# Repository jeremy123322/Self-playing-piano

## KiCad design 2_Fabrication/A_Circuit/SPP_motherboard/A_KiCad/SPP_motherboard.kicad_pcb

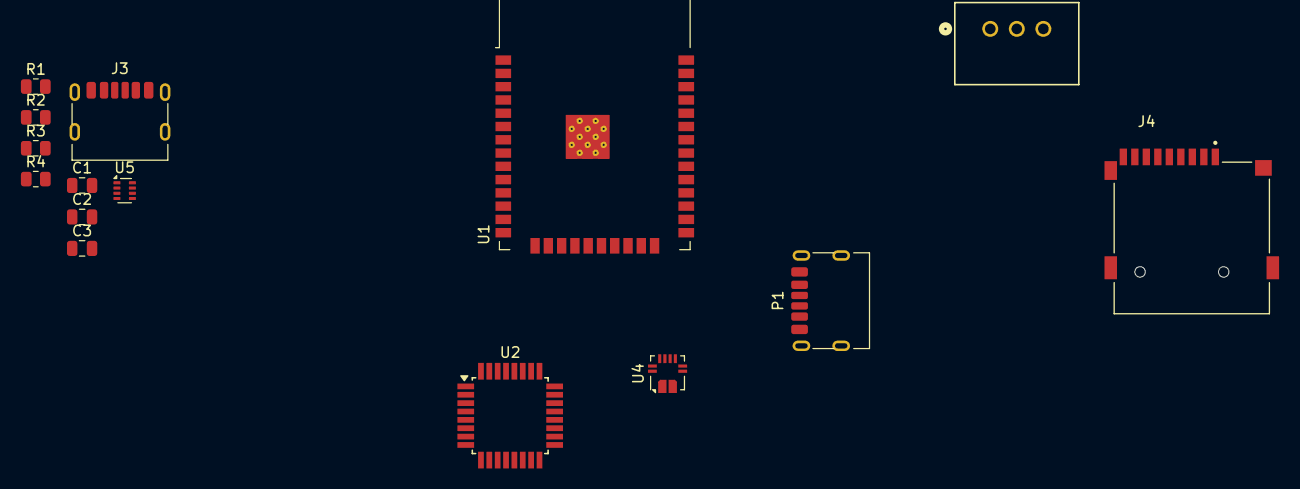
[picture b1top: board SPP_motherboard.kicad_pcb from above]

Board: 2 copper layers, 15 parts (0 on the bottom side), 13 nets, no tracks yet.

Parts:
C1: 100nF; C_0805_2012Metric
C2: 10uF; C_0805_2012Metric
C3: 22uF; C_0805_2012Metric
J3: USB_C_Receptacle_USB2.0_14P; USB_C_Receptacle_HRO_TYPE-C-31-M-17
J4: Micro_SD_Card; CUI_MSD-1-A
P1: USB_C_Plug_USB2.0; USB_C_Receptacle_HRO_TYPE-C-31-M-17
R1, R2: 5.1k; R_0805_2012Metric
R3, R4: R; R_0805_2012Metric
U1: ESP32-WROOM-32
U2: ATmega328P-A; TQFP-32_7x7mm_P0.8mm
U2#2: RBT10W24S05; RBT10W24S05_XPP_XPR
U4: ACS711xEXLT-31AB; Allegro_QFN-12-10-1EP_3x3mm_P0.5mm
U5: TPS2116DRL; SOT-583-8

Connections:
+3V3: C1.1, C3.1, U4.10 (VCC)
+5V,DC/DC: U2#2.3 (Vout), U5.6 (VIN2)
+24V: U2#2.1 (Vin), U4.2 (IP-)
GND: C1.2, C2.2, C3.2, J3.A12 (GND), J3.B12 (GND), J3.S1 (SHIELD), R1.2, R2.2, R4.2, U2#2.2 (GND), U4.3 (GND), U5.1 (GND)
unnamed: J3.A5 (CC1), R2.1
unnamed: J3.B5 (CC2), R1.1
unnamed: P1.A12 (GND), P1.B12 (GND)
unnamed: P1.A9 (VBUS), P1.B9 (VBUS)
unnamed: U1.1 (GND), U1.15 (GND), U1.38 (GND), U1.39 (GND)
unnamed: U2.3 (GND), U2.5 (GND), U2.21 (GND)
unnamed: U2.4 (VCC), U2.6 (VCC)
unnamed: R3.2, R4.1, U5.4 (PR1)
VBUS: J3.A9 (VBUS), J3.B9 (VBUS), R3.1, U5.3 (VIN1), U5.5 (MODE)

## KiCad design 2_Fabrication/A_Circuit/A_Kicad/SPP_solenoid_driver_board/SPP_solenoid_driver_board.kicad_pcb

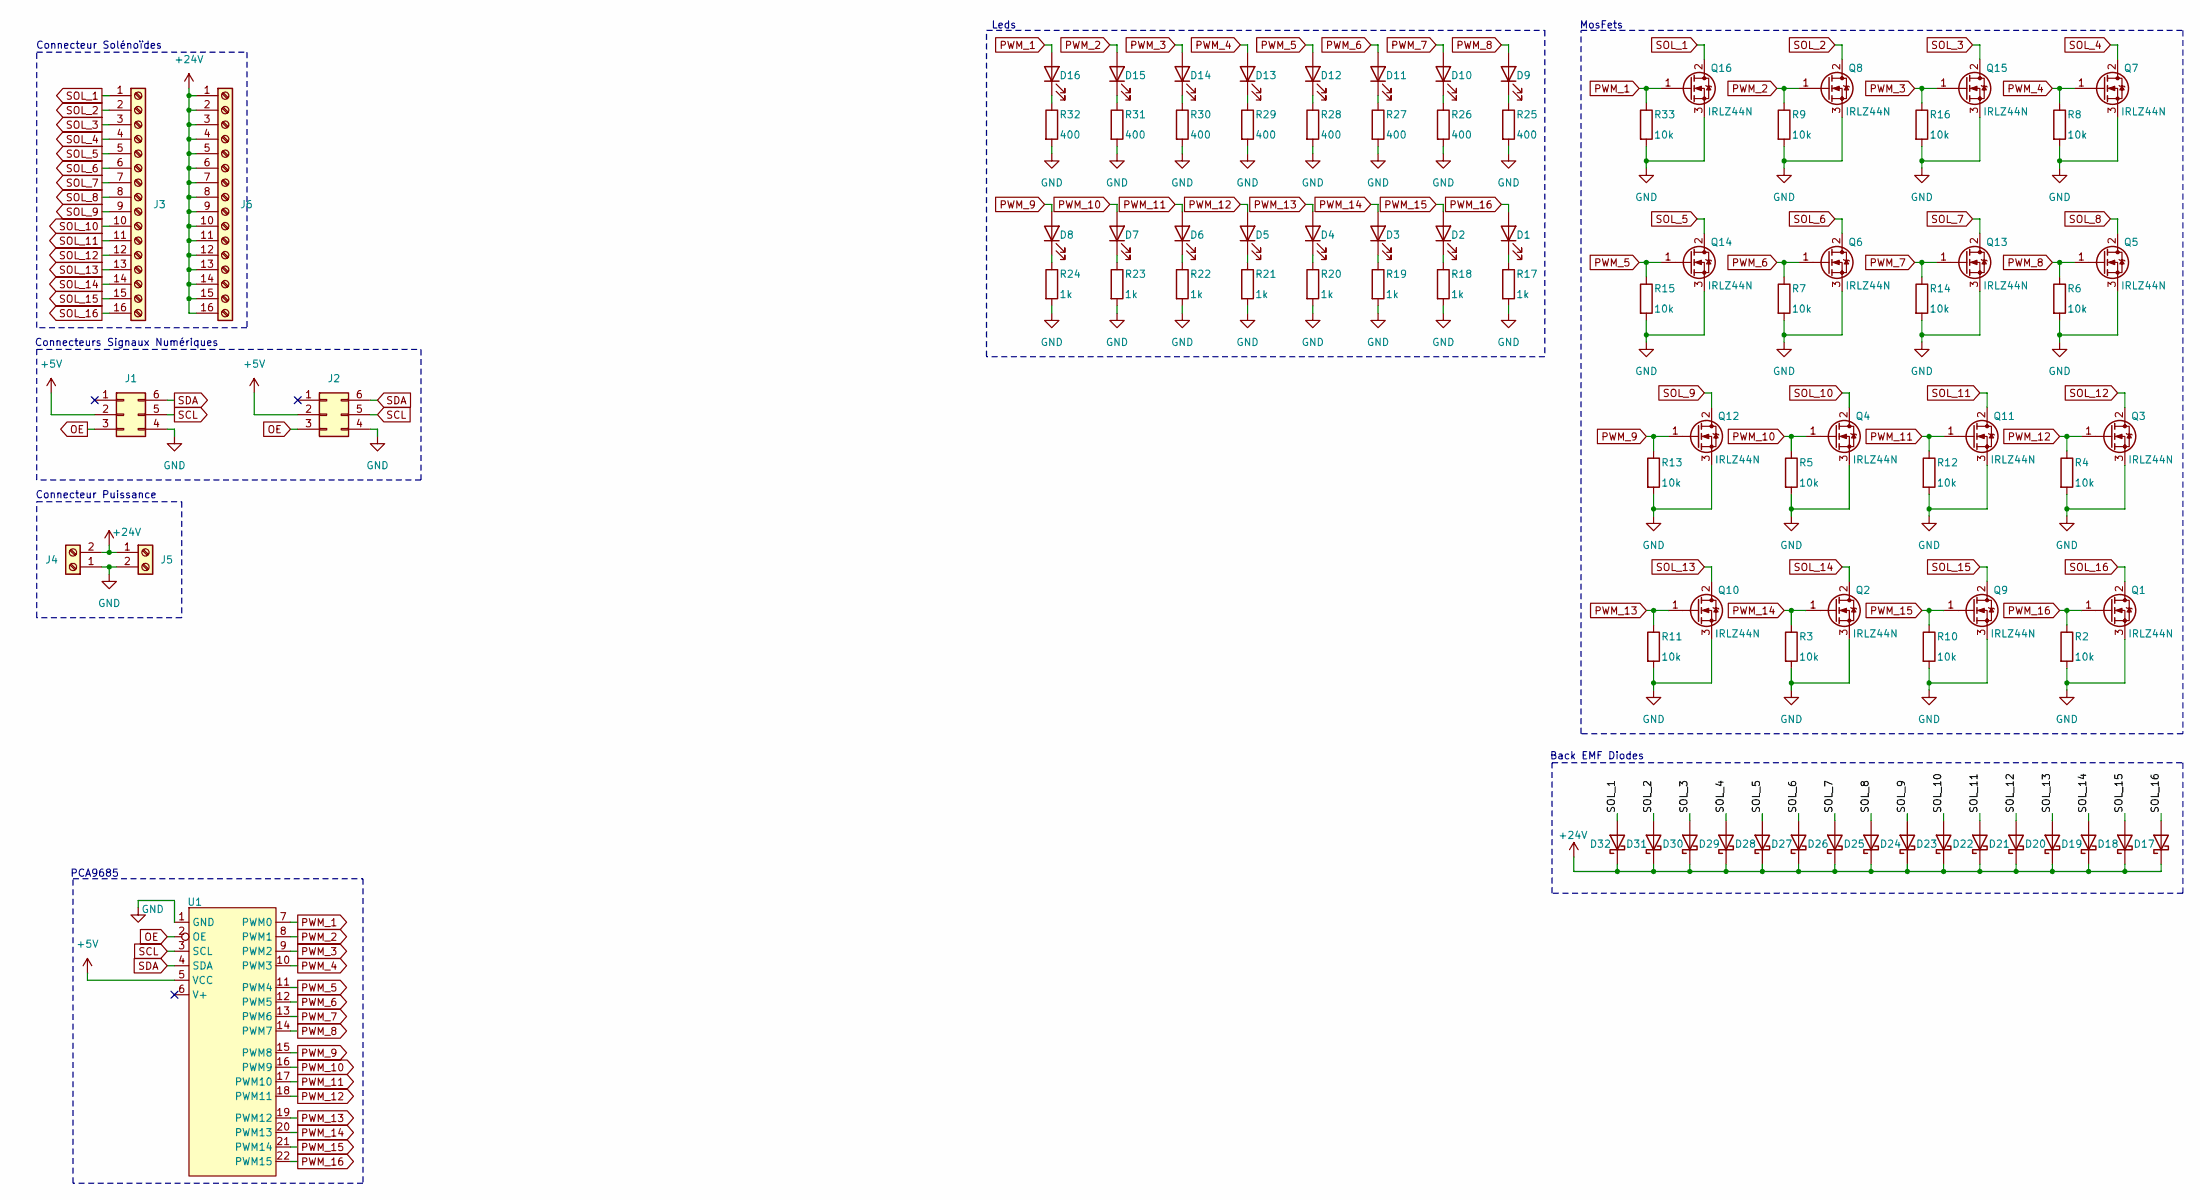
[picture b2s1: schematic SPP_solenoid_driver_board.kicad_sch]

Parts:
D1, D2, D3, D4, D5, D6, D7, D8, D9, D10, D11, D12, D13, D14, D15, D16: LED; LED_D5.0mm_Clear
D17, D18, D19, D20, D21, D22, D23, D24, D25, D26, D27, D28, D29, D30, D31, D32: 1N5819; D_DO-41_SOD81_P10.16mm_Horizontal
J1, J2: Conn_02x03_Counter_Clockwise; IDC-Header_2x03_P2.54mm_Vertical
J3, J6: Screw_Terminal_01x16; TerminalBlock_Phoenix_PT-1,5-16-5.0-H_1x16_P5.00mm_Horizont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
J4, J5: Screw_Terminal_01x02; TerminalBlock_Phoenix_MKDS-1,5-2_1x02_P5.00mm_Horizontal
Q1, Q2, Q3, Q4, Q5, Q6, Q7, Q8, Q9, Q10, Q11, Q12, Q13, Q14, Q15, Q16: IRLZ44N; TO-220-3_Vertical
R2, R3, R4, R5, R6, R7, R8, R9, R10, R11, R12, R13, R14, R15, R16, R33: 10k; R_1206_3216Metric
R17, R18, R19, R20, R21, R22, R23, R24: 1k; R_1206_3216Metric
R25, R26, R27, R28, R29, R30, R31, R32: 400; R_1206_3216Metric
U1: PCA9685_Devkit

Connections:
+5V: J1.2, J2.2, U1.5 (VCC)
+24V: D17.1 (K), D18.1 (K), D19.1 (K), D20.1 (K), D21.1 (K), D22.1 (K), D23.1 (K), D24.1 (K), D25.1 (K), D26.1 (K), D27.1 (K), D28.1 (K), D29.1 (K), D30.1 (K), D31.1 (K), D32.1 (K), J4.2, J5.1, J6.1, J6.2, J6.3, J6.4, J6.5, J6.6, J6.7, J6.8, J6.9, J6.10, J6.11, J6.12, J6.13, J6.14, J6.15, J6.16
GND: J1.4, J2.4, J4.1, J5.2, Q1.3 (S), Q2.3 (S), Q3.3 (S), Q4.3 (S), Q5.3 (S), Q6.3 (S), Q7.3 (S), Q8.3 (S), Q9.3 (S), Q10.3 (S), Q11.3 (S), Q12.3 (S), Q13.3 (S), Q14.3 (S), Q15.3 (S), Q16.3 (S), R2.2, R3.2, R4.2, R5.2, R6.2, R7.2, R8.2, R9.2, R10.2, R11.2, R12.2, R13.2, R14.2, R15.2, R16.2, R17.2, R18.2, R19.2, R20.2, R21.2, R22.2, R23.2, R24.2, R25.2, R26.2, R27.2, R28.2, R29.2, R30.2, R31.2, R32.2, R33.2, U1.1 (GND)
unnamed: D1.1 (K), R17.1
unnamed: D2.1 (K), R18.1
unnamed: D3.1 (K), R19.1
unnamed: D4.1 (K), R20.1
unnamed: D5.1 (K), R21.1
unnamed: D6.1 (K), R22.1
unnamed: D7.1 (K), R23.1
unnamed: D8.1 (K), R24.1
unnamed: D9.1 (K), R25.1
unnamed: D10.1 (K), R26.1
unnamed: D11.1 (K), R27.1
unnamed: D12.1 (K), R28.1
unnamed: D13.1 (K), R29.1
unnamed: D14.1 (K), R30.1
unnamed: D15.1 (K), R31.1
unnamed: D16.1 (K), R32.1
OE: J1.3, J2.3, U1.2 (OE)
PWM_1: D16.2 (A), Q16.1 (G), R33.1, U1.7 (PWM0)
PWM_2: D15.2 (A), Q8.1 (G), R9.1, U1.8 (PWM1)
PWM_3: D14.2 (A), Q15.1 (G), R16.1, U1.9 (PWM2)
PWM_4: D13.2 (A), Q7.1 (G), R8.1, U1.10 (PWM3)
PWM_5: D12.2 (A), Q14.1 (G), R15.1, U1.11 (PWM4)
PWM_6: D11.2 (A), Q6.1 (G), R7.1, U1.12 (PWM5)
PWM_7: D10.2 (A), Q13.1 (G), R14.1, U1.13 (PWM6)
PWM_8: D9.2 (A), Q5.1 (G), R6.1, U1.14 (PWM7)
PWM_9: D8.2 (A), Q12.1 (G), R13.1, U1.15 (PWM8)
PWM_10: D7.2 (A), Q4.1 (G), R5.1, U1.16 (PWM9)
PWM_11: D6.2 (A), Q11.1 (G), R12.1, U1.17 (PWM10)
PWM_12: D5.2 (A), Q3.1 (G), R4.1, U1.18 (PWM11)
PWM_13: D4.2 (A), Q10.1 (G), R11.1, U1.19 (PWM12)
PWM_14: D3.2 (A), Q2.1 (G), R3.1, U1.20 (PWM13)
PWM_15: D2.2 (A), Q9.1 (G), R10.1, U1.21 (PWM14)
PWM_16: D1.2 (A), Q1.1 (G), R2.1, U1.22 (PWM15)
SCL: J1.5, J2.5, U1.3 (SCL)
SDA: J1.6, J2.6, U1.4 (SDA)
SOL_1: D32.2 (A), J3.1, Q16.2 (D)
SOL_2: D31.2 (A), J3.2, Q8.2 (D)
SOL_3: D30.2 (A), J3.3, Q15.2 (D)
SOL_4: D29.2 (A), J3.4, Q7.2 (D)
SOL_5: D28.2 (A), J3.5, Q14.2 (D)
SOL_6: D27.2 (A), J3.6, Q6.2 (D)
SOL_7: D26.2 (A), J3.7, Q13.2 (D)
SOL_8: D25.2 (A), J3.8, Q5.2 (D)
SOL_9: D24.2 (A), J3.9, Q12.2 (D)
SOL_10: D23.2 (A), J3.10, Q4.2 (D)
SOL_11: D22.2 (A), J3.11, Q11.2 (D)
SOL_12: D21.2 (A), J3.12, Q3.2 (D)
SOL_13: D20.2 (A), J3.13, Q10.2 (D)
SOL_14: D19.2 (A), J3.14, Q2.2 (D)
SOL_15: D18.2 (A), J3.15, Q9.2 (D)
SOL_16: D17.2 (A), J3.16, Q1.2 (D)

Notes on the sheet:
Back EMF Diodes
MosFets
Leds
PCA9685
Connecteurs Signaux Numériques
Connecteur Puissance
Connecteur Solénoïdes

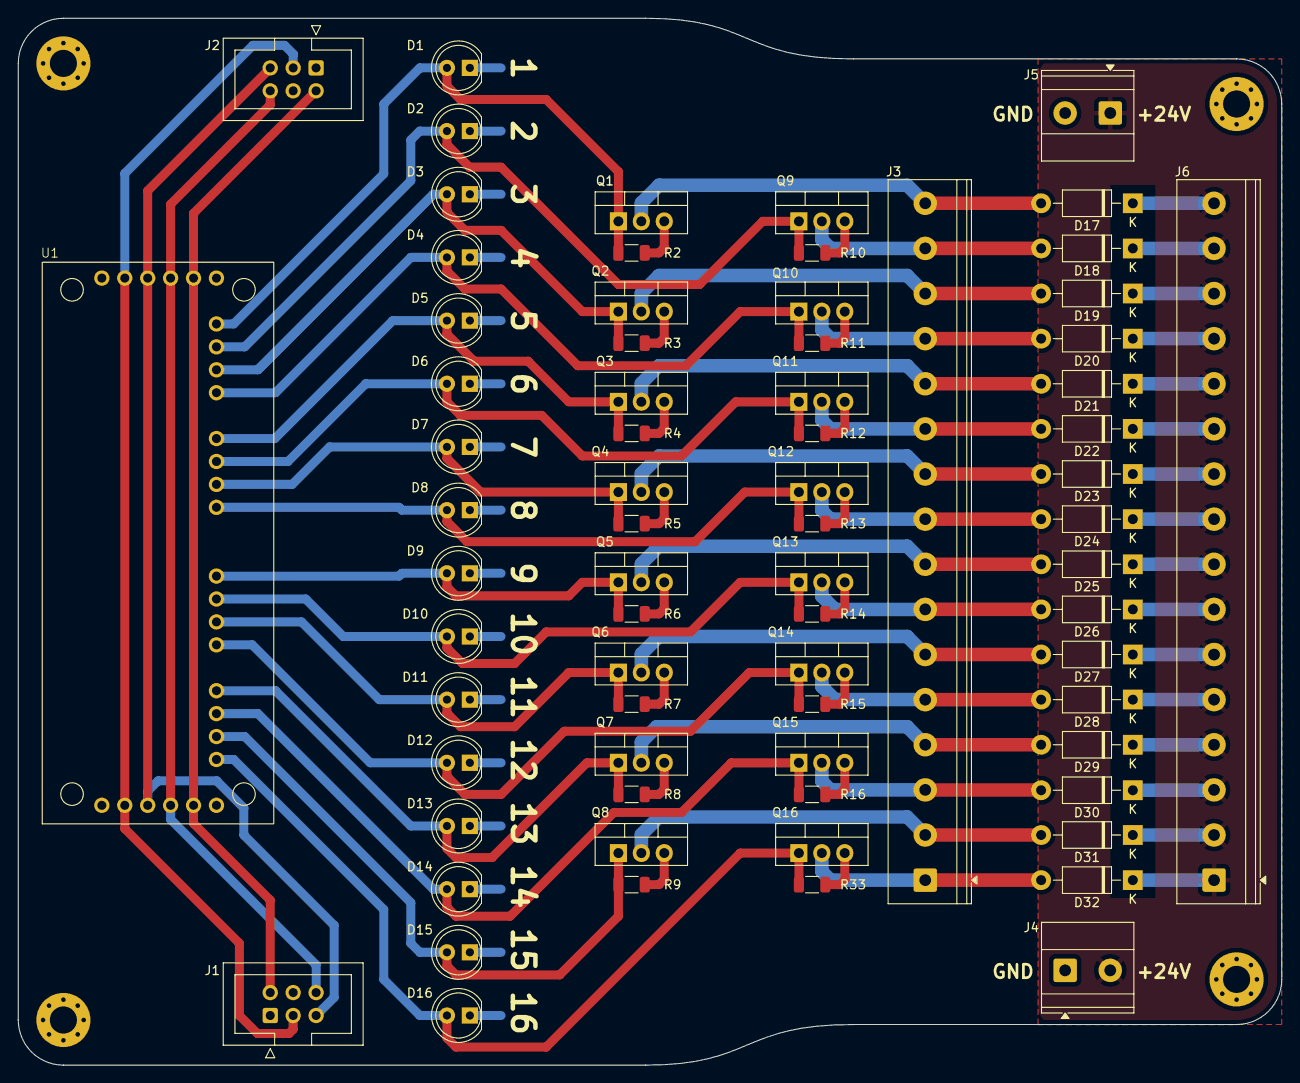
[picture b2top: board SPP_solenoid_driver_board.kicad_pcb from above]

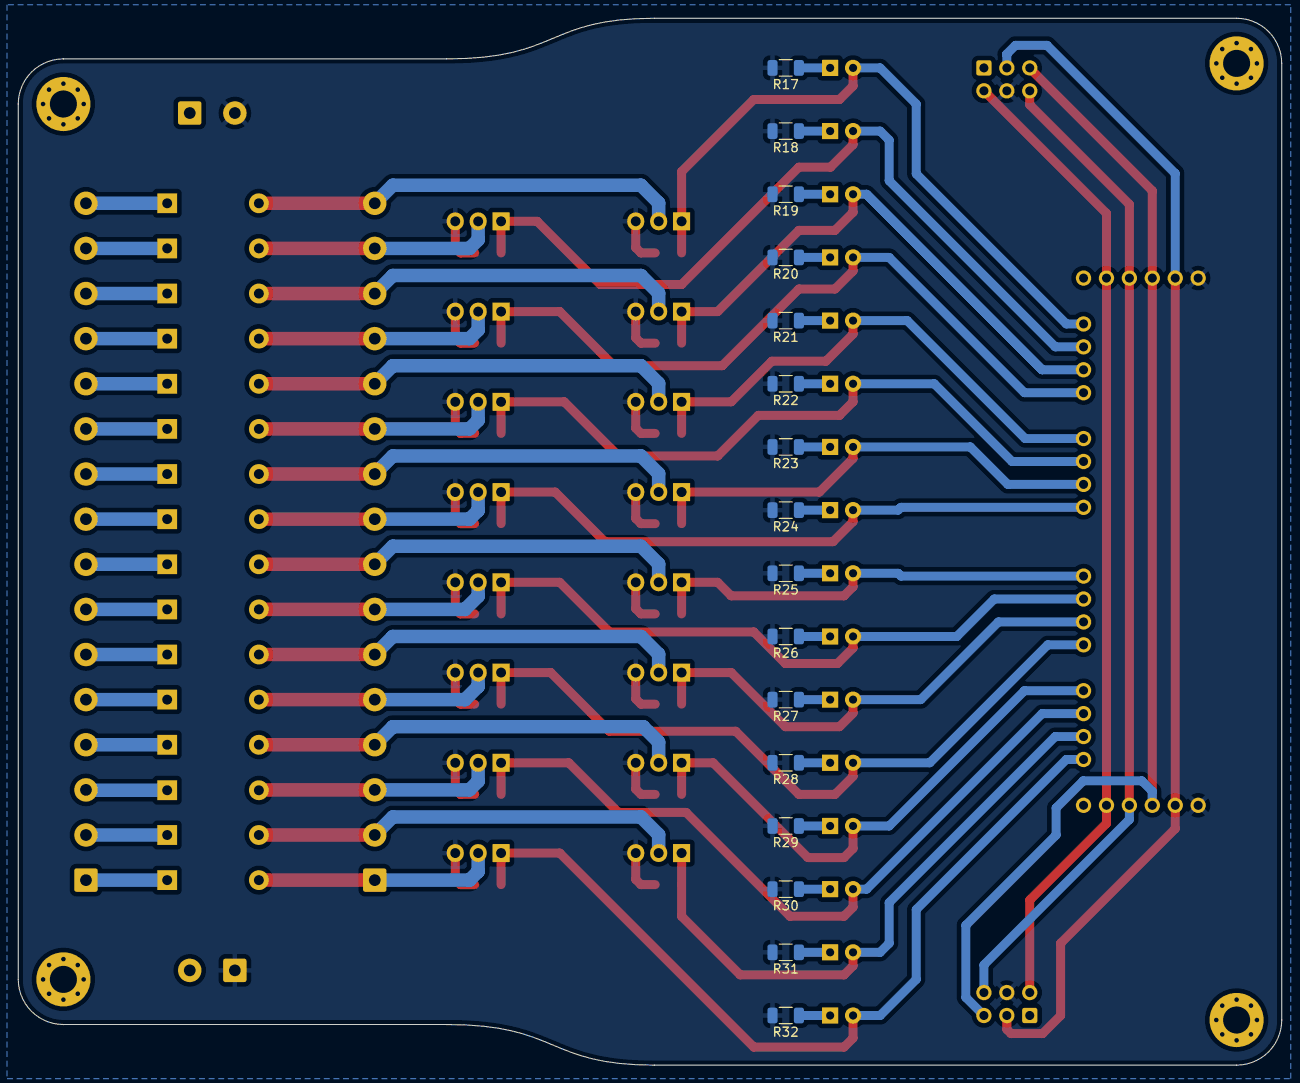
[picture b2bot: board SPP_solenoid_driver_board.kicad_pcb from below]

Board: 2 copper layers, 140.0 x 116.0 mm, 87 parts (16 on the bottom side), 54 nets.
